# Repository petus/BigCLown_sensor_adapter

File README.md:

# BigClown_sensor_adapter v0.2 (development phase)</br>
Sensor adapter for BigClown IoT platform</br>
</br>
This adapter is used like bridge between BigClown Core module and chinese sensors</br>
</br>
More info: </br>
www.chiptron.cz (czech language) https://chiptron.cz/articles.php?article_id=194</br>
www.time4ee.com (english language) https://time4ee.com/articles.php?article_id=119</br>
<br>

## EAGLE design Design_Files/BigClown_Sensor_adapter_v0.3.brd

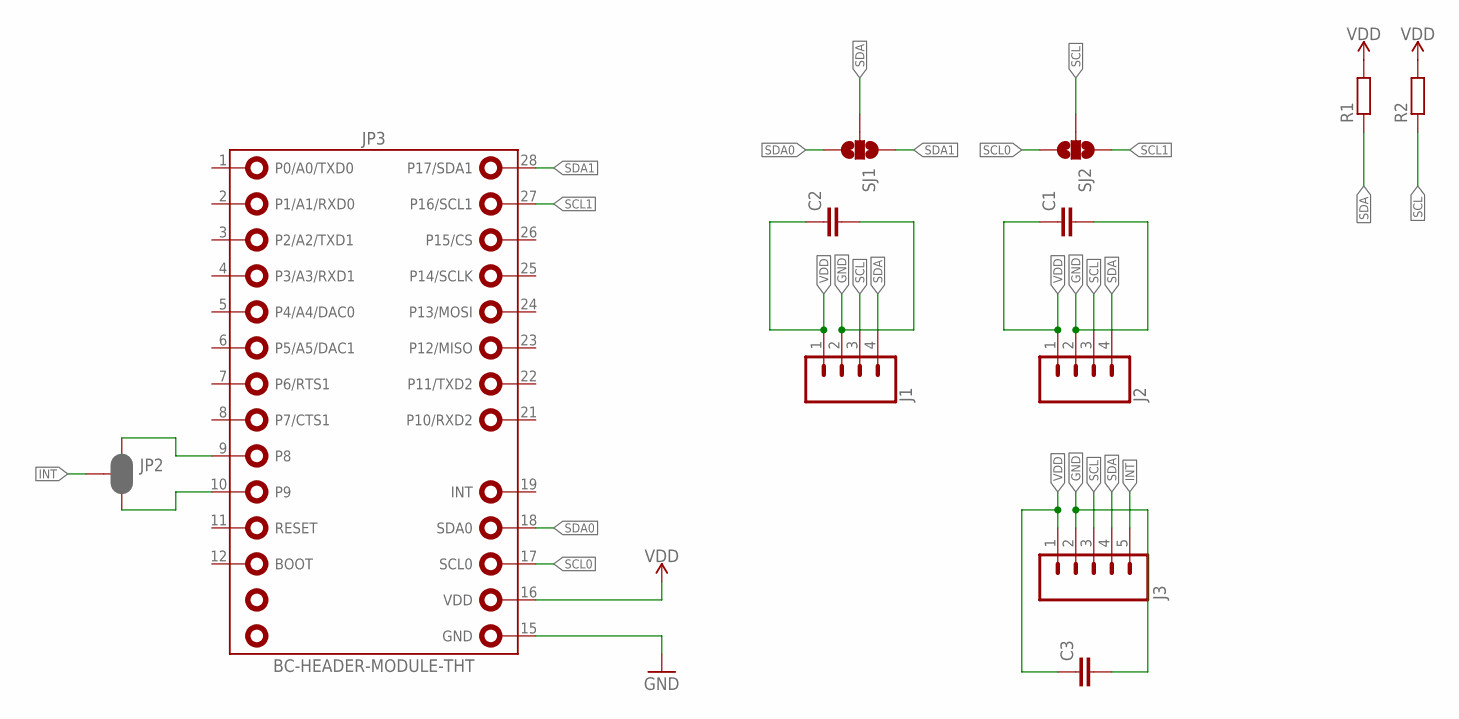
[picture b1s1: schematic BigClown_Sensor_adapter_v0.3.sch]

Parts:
C1, C2, C3: C-EUC0805; C0805
J1, J2: CONN_04LONGPADS; 1X04_LONGPADS
J3: M05PTH_LONGPADS; 1X05_LONGPADS
JP2: JUMPER-SMT_3_2-NC_PASTE_SILK; SMT-JUMPER_3_2-NC_PASTE_SILK
JP3: BC-HEADER-MODULE-THT
R1, R2: R-EU_M0805; M0805
SJ1, SJ2: SOLDERJUMPER_2WAYS; SJ_3

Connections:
GND: C1.2, C2.2, C3.2, J1.2, J2.2, J3.2, JP3.15 (GND)
INT: J3.5, JP2.2
unnamed: JP2.3, JP3.10 (P9)
unnamed: JP2.1, JP3.9 (P8)
SCL: J1.3, J2.3, J3.3, R2.1, SJ2.2
SCL0: JP3.17 (SCL0), SJ2.3
SCL1: JP3.27 (P16/SCL1), SJ2.1
SDA: J1.4, J2.4, J3.4, R1.1, SJ1.2
SDA0: JP3.18 (SDA0), SJ1.3
SDA1: JP3.28 (P17/SDA1), SJ1.1
VDD: C1.1, C2.1, C3.1, J1.1, J2.1, J3.1, JP3.16 (VDD), R1.2, R2.2

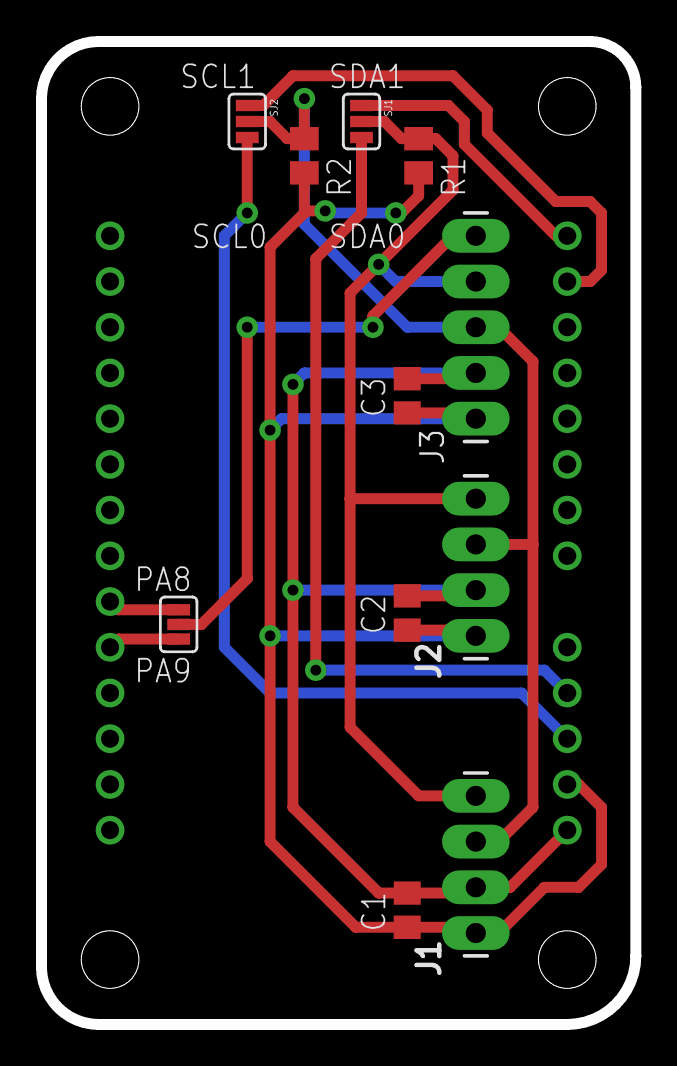
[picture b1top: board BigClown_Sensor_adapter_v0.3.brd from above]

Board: 2 copper layers, 33.0 x 54.6 mm, 12 parts (0 on the bottom side), 11 nets.

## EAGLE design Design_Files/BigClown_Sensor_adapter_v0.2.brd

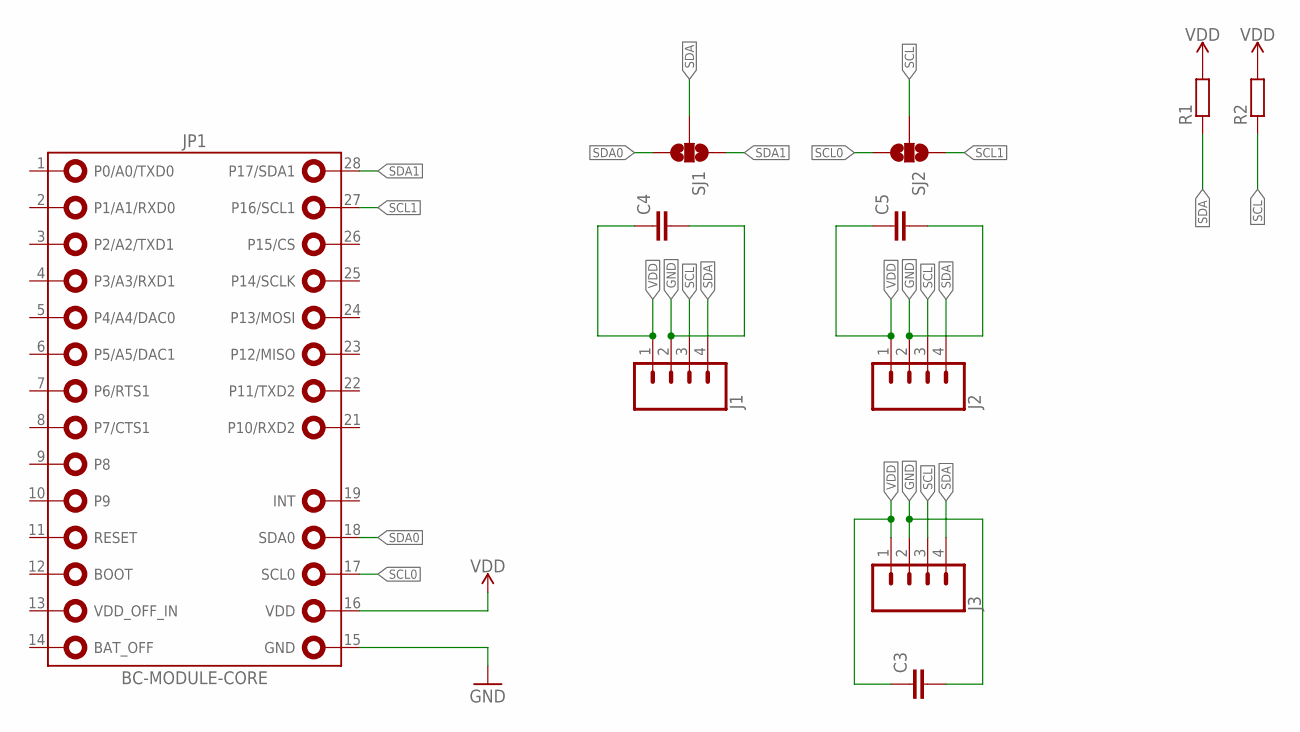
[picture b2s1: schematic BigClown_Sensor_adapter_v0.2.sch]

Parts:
C3, C4, C5: C-EUC0805; C0805
J1, J2, J3: CONN_04LONGPADS; 1X04_LONGPADS
JP1: BC-MODULE-CORE
R1, R2: R-EU_M0805; M0805
SJ1, SJ2: SOLDERJUMPER_2WAYS; SJ_3

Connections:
GND: C3.2, C4.2, C5.2, J1.2, J2.2, J3.2, JP1.15 (GND)
SCL: J1.3, J2.3, J3.3, R2.1, SJ2.2
SCL0: JP1.17 (SCL0), SJ2.3
SCL1: JP1.27 (P16/SCL1), SJ2.1
SDA: J1.4, J2.4, J3.4, R1.1, SJ1.2
SDA0: JP1.18 (SDA0), SJ1.3
SDA1: JP1.28 (P17/SDA1), SJ1.1
VDD: C3.1, C4.1, C5.1, J1.1, J2.1, J3.1, JP1.16 (VDD), R1.2, R2.2

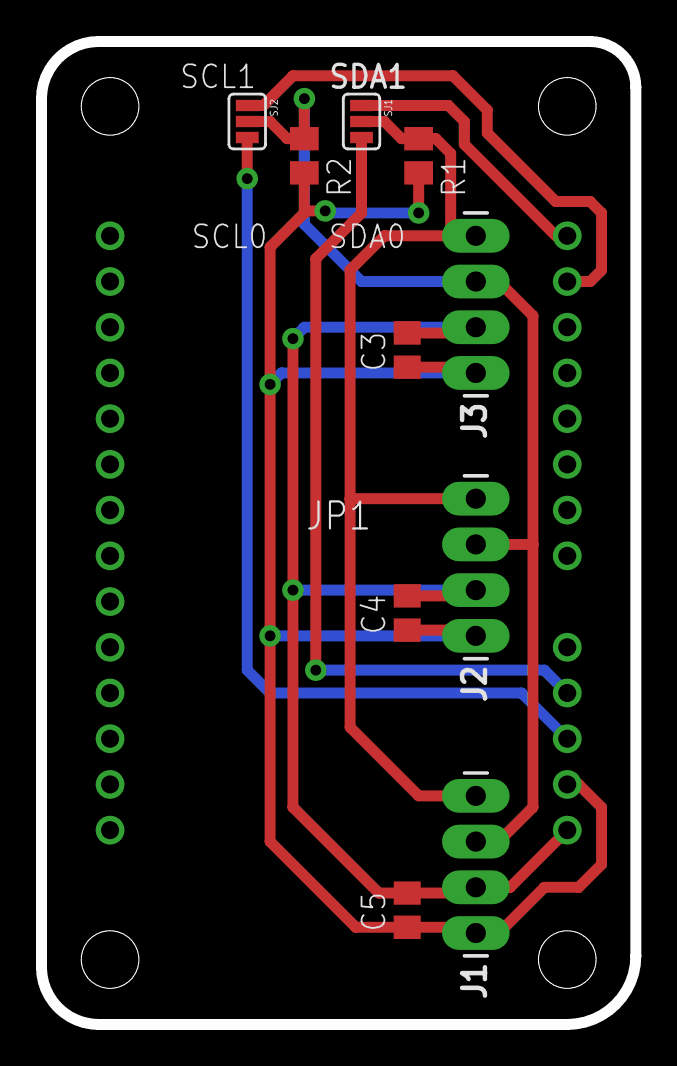
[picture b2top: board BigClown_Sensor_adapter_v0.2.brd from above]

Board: 2 copper layers, 33.0 x 54.6 mm, 11 parts (0 on the bottom side), 8 nets.

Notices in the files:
parts and their libraries:
SparkFun-Connectors: Licensing: Creative Commons ShareAlike 4.0 International - https://creativecommons.org/licenses/by-sa/4.0
SparkFun: Licensing: CC v3.0 Share-Alike You are welcome to use this library for commercial purposes.
